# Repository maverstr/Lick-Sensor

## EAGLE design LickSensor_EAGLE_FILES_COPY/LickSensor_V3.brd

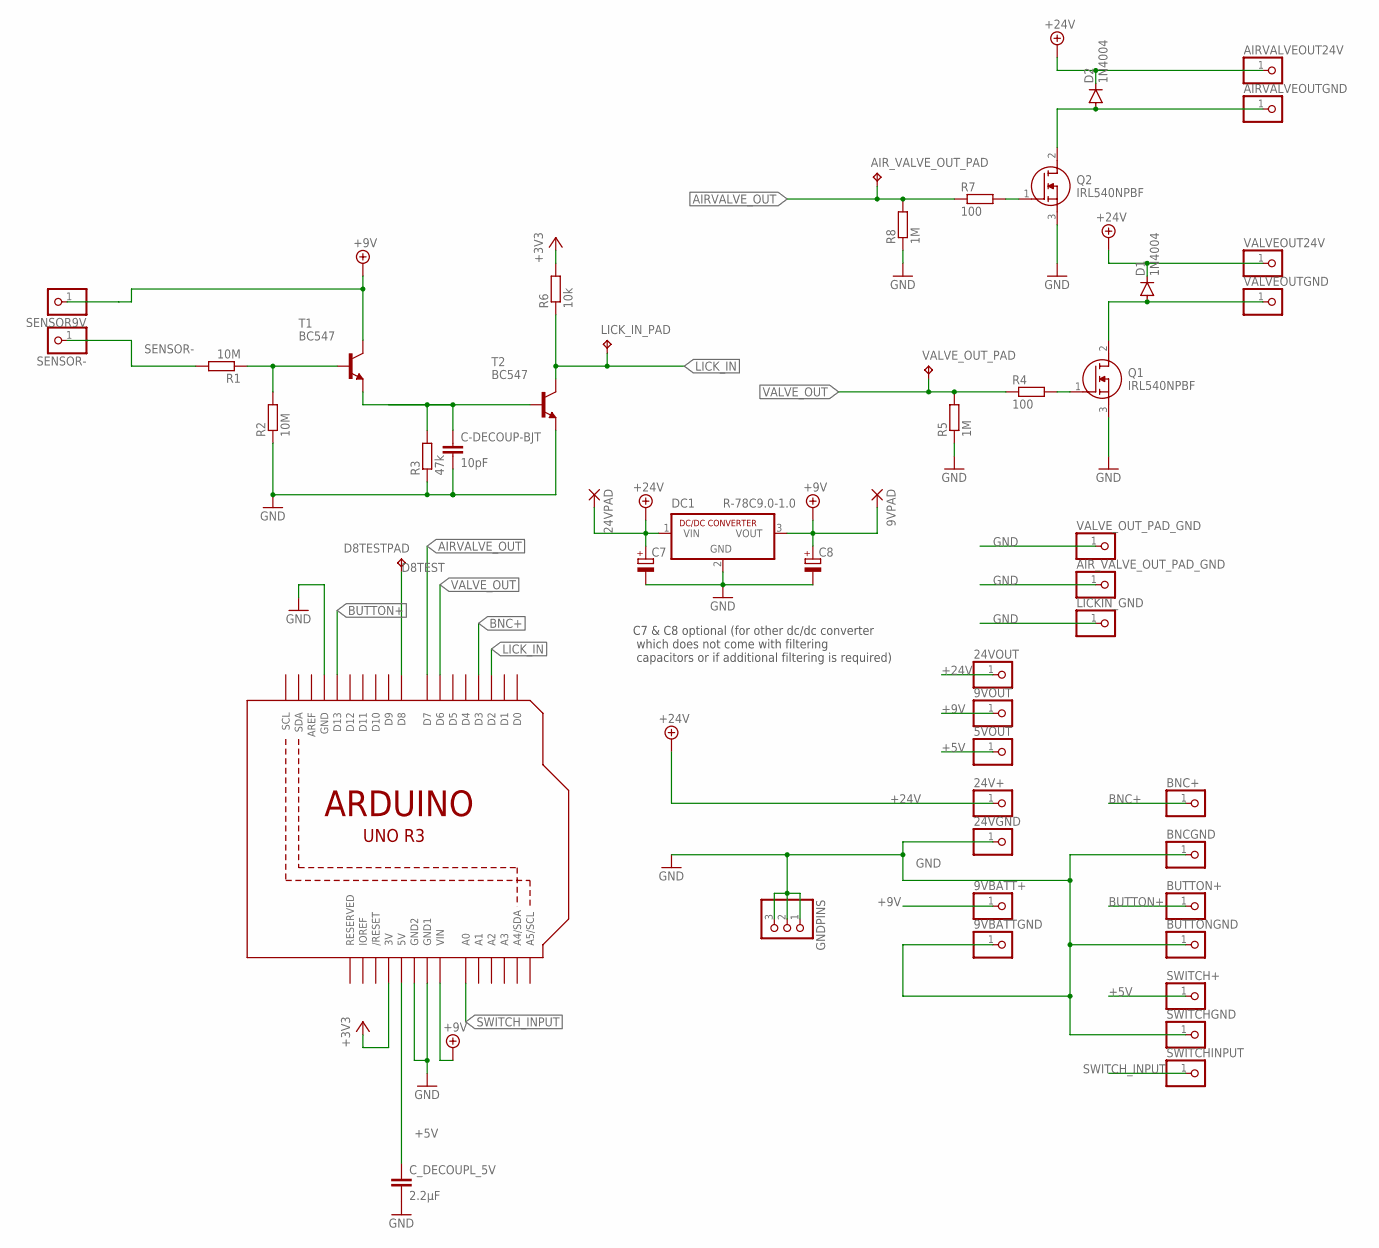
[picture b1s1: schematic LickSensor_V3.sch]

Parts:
5VOUT, 9VBATT+, 9VBATTGND, 9VOUT, 24V+, 24VGND, 24VOUT: PINHD-1X1; 1X01
9VPAD, 24VPAD: 1,6/0,8
AIRVALVEOUT24V: PINHD-1X1; 1X01
AIRVALVEOUTGND: PINHD-1X1; 1X01
AIR_VALVE_OUT_PAD: TPPAD1-13; P1-13
AIR_VALVE_OUT_PAD_GND: PINHD-1X1; 1X01
BNC+: PINHD-1X1; 1X01
BNCGND: PINHD-1X1; 1X01
BUTTON+: PINHD-1X1; 1X01
BUTTONGND: PINHD-1X1; 1X01
C7, C8: CPOL-EUTT2D6; TT2D6
C-DECOUP-BJT: 10pF; C050-030X075
C_DECOUPL_5V: 2.2µF; C050-030X075
D1, D2: 1N4004; DO41-10
D8TESTPAD: TPPAD1-13; P1-13
DC1: R-78C9.0-1.0; SIP3
GNDPINS: PINHD-1X3; 1X03
LICKIN_GND: PINHD-1X1; 1X01
LICK_IN_PAD: TPPAD1-13; P1-13
Q1, Q2: IRL540NPBF; TO254P469X1042X1967-3P
R1, R2: 10M; 0207/7
R3: 47k; 0207/7
R4, R7: 100; 0204/7
R5, R8: 1M; 0204/7
R6: 10k; 0204/7
SENSOR9V: PINHD-1X1; 1X01
SENSOR-: PINHD-1X1; 1X01
SWITCH+: PINHD-1X1; 1X01
SWITCHGND: PINHD-1X1; 1X01
SWITCHINPUT: PINHD-1X1; 1X01
T1, T2: BC547; TO92
U1: ARDUINOR3-DIMENSION; ARDUINOR3
VALVEOUT24V: PINHD-1X1; 1X01
VALVEOUTGND: PINHD-1X1; 1X01
VALVE_OUT_PAD: TPPAD1-13; P1-13
VALVE_OUT_PAD_GND: PINHD-1X1; 1X01

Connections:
+3V3: R6.2, U1.3V
+5V: 5VOUT.1, C_DECOUPL_5V.1, SWITCH+.1, U1.5V
+9V: 9VBATT+.1, 9VOUT.1, 9VPAD.1, C8.+, DC1.3 (VOUT), SENSOR9V.1, T1.3 (C), U1.VIN
+24V: 24V+.1, 24VOUT.1, 24VPAD.1, AIRVALVEOUT24V.1, C7.+, D1.C, D2.C, DC1.1 (VIN), VALVEOUT24V.1
AIRVALVE_OUT: AIR_VALVE_OUT_PAD.TP, R7.1, R8.2, U1.D7
BNC+: BNC+.1, U1.D3
BUTTON+: BUTTON+.1, U1.D13
D8TEST: D8TESTPAD.TP, U1.D8
GND: 9VBATTGND.1, 24VGND.1, AIR_VALVE_OUT_PAD_GND.1, BNCGND.1, BUTTONGND.1, C7.-, C8.-, C-DECOUP-BJT.2, C_DECOUPL_5V.2, DC1.2 (GND), GNDPINS.1, GNDPINS.2, GNDPINS.3, LICKIN_GND.1, Q1.3 (S), Q2.3 (S), R2.1, R3.1, R5.1, R8.1, SWITCHGND.1, T2.1 (E), U1.GND, U1.GND1, U1.GND2, VALVE_OUT_PAD_GND.1
GND1: D1.A, Q1.2 (D), VALVEOUTGND.1
GND2: AIRVALVEOUTGND.1, D2.A, Q2.2 (D)
LICK_IN: LICK_IN_PAD.TP, R6.1, T2.3 (C), U1.D2
unnamed: Q2.1 (G), R7.2
unnamed: Q1.1 (G), R4.2
unnamed: C-DECOUP-BJT.1, R3.2, T1.1 (E), T2.2 (B)
unnamed: R1.1, R2.2, T1.2 (B)
SENSOR-: R1.2, SENSOR-.1
SWITCH_INPUT: SWITCHINPUT.1, U1.A0
VALVE_OUT: R4.1, R5.2, U1.D6, VALVE_OUT_PAD.TP

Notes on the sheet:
C7 & C8 optional (for other dc/dc converter which does not come with filtering capacitors or if additional filtering is required)

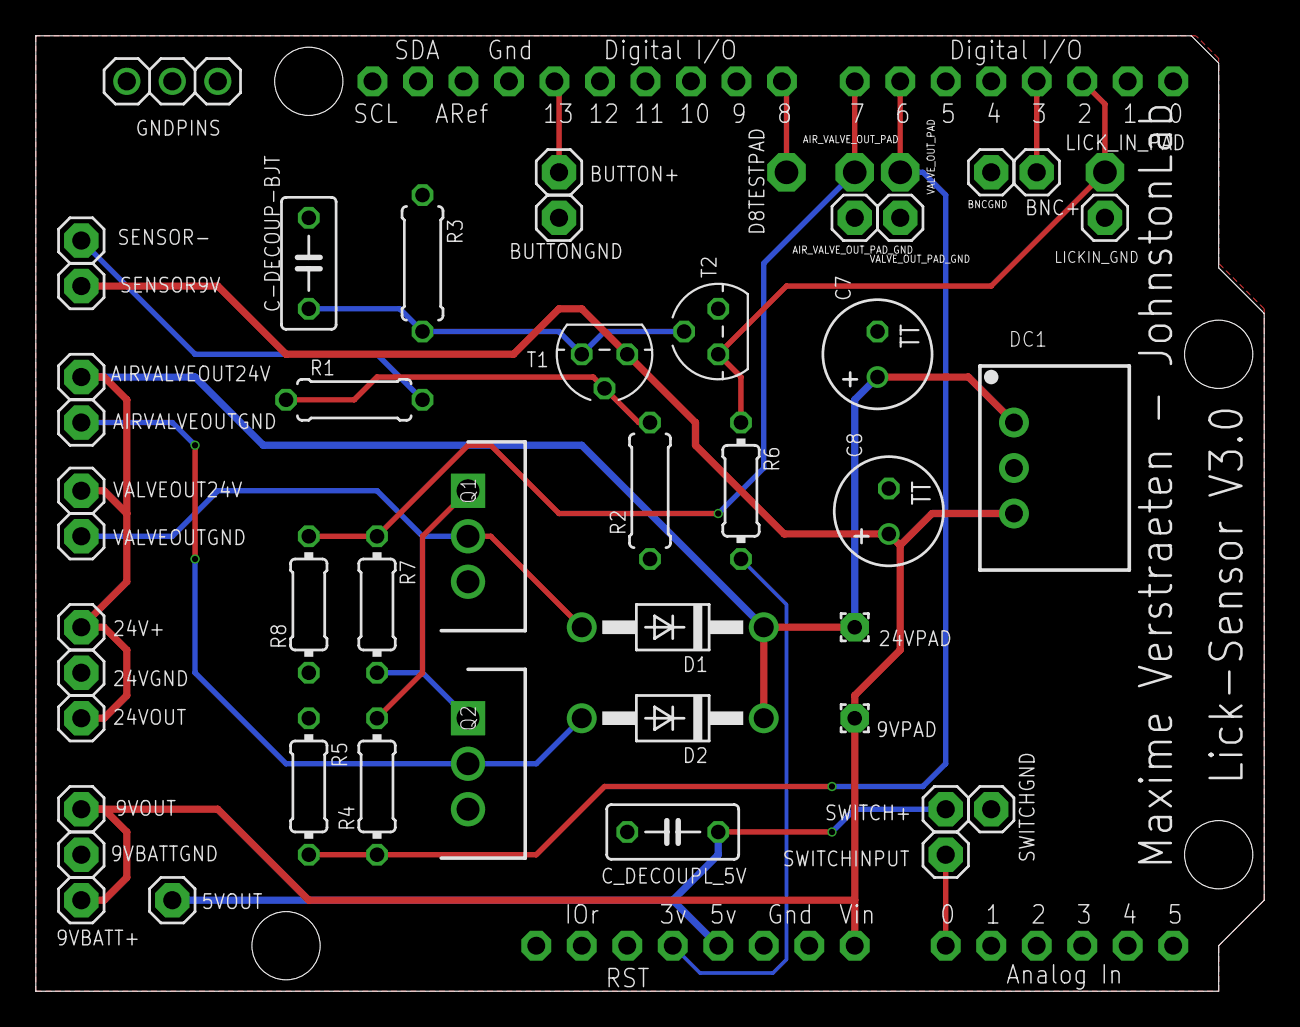
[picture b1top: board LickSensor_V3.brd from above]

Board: 2 copper layers, 68.6 x 53.3 mm, 50 parts (0 on the bottom side), 19 nets.

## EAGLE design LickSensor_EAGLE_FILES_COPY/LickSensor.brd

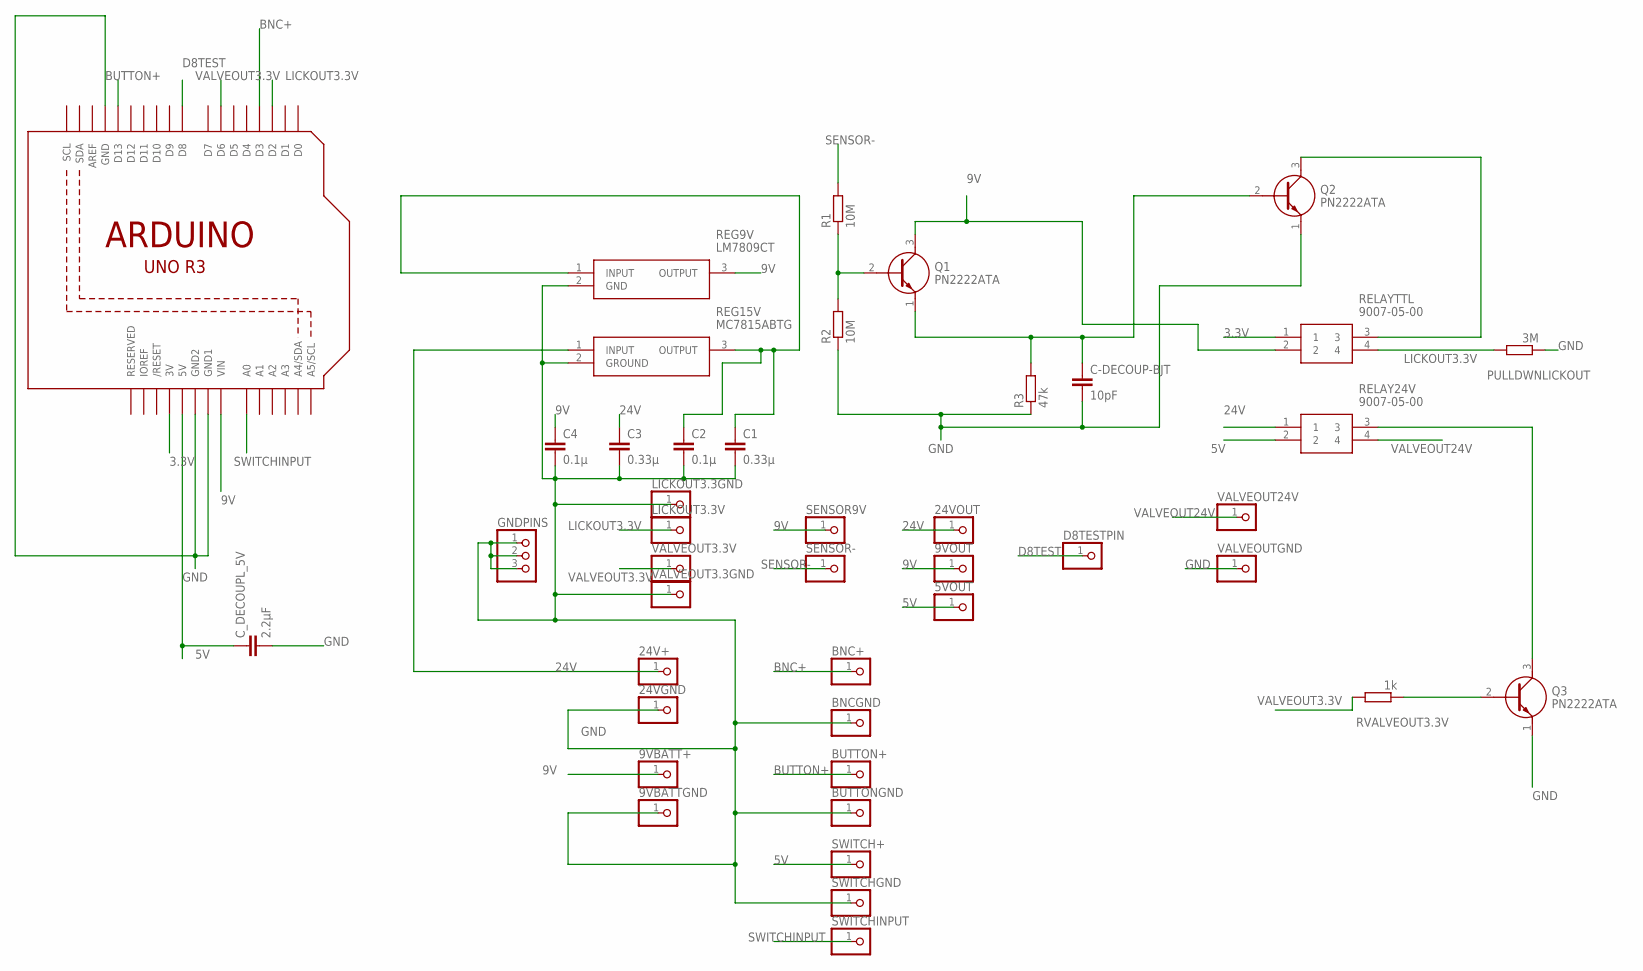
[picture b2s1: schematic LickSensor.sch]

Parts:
5VOUT, 9VBATT+, 9VBATTGND, 9VOUT, 24V+, 24VGND, 24VOUT: PINHD-1X1; 1X01
BNC+: PINHD-1X1; 1X01
BNCGND: PINHD-1X1; 1X01
BUTTON+: PINHD-1X1; 1X01
BUTTONGND: PINHD-1X1; 1X01
C1, C3: 0.33µ; C5B2.5
C2, C4: 0.1µ; C5B2.5
C-DECOUP-BJT: 10pF; C050-030X075
C_DECOUPL_5V: 2.2µF; C050-030X075
D8TESTPIN: PINHD-1X1; 1X01
GNDPINS: PINHD-1X3; 1X03
LICKOUT3.3GND, LICKOUT3.3V: PINHD-1X1; 1X01
PULLDWNLICKOUT: 3M; 0207/10
Q1, Q2, Q3: PN2222ATA; TO-92-3
R1, R2: 10M; 0207/7
R3: 47k; 0207/7
REG9V: LM7809CT; TO254P470X1016X2019-3P
REG15V: MC7815ABTG; TO254P482X997X2018-3P
RELAY24V: 9007-05-00; 9007
RELAYTTL: 9007-05-00; 9007
RVALVEOUT3.3V: 1k; 0207/10
SENSOR9V: PINHD-1X1; 1X01
SENSOR-: PINHD-1X1; 1X01
SWITCH+: PINHD-1X1; 1X01
SWITCHGND: PINHD-1X1; 1X01
SWITCHINPUT: PINHD-1X1; 1X01
U1: ARDUINOR3-DIMENSION; ARDUINOR3
VALVEOUT3.3GND, VALVEOUT3.3V, VALVEOUT24V: PINHD-1X1; 1X01
VALVEOUTGND: PINHD-1X1; 1X01

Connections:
3.3V: RELAYTTL.1, U1.3V
5V: 5VOUT.1, C_DECOUPL_5V.1, RELAY24V.2, SWITCH+.1, U1.5V
9V: 9VBATT+.1, 9VOUT.1, C4.1, Q1.3 (C), REG9V.3 (OUTPUT), RELAYTTL.2, SENSOR9V.1, U1.VIN
24V: 24V+.1, 24VOUT.1, C3.1, REG15V.1 (INPUT), RELAY24V.1
BNC+: BNC+.1, U1.D3
BUTTON+: BUTTON+.1, U1.D13
D8TEST: D8TESTPIN.1, U1.D8
GND: 9VBATTGND.1, 24VGND.1, BNCGND.1, BUTTONGND.1, C1.2, C2.2, C3.2, C4.2, C-DECOUP-BJT.2, C_DECOUPL_5V.2, GNDPINS.1, GNDPINS.2, GNDPINS.3, LICKOUT3.3GND.1, PULLDWNLICKOUT.1, Q2.1 (E), Q3.1 (E), R2.1, R3.1, REG9V.2 (GND), REG15V.2 (GROUND), SWITCHGND.1, U1.GND, U1.GND1, U1.GND2, VALVEOUT3.3GND.1, VALVEOUTGND.1
LICKOUT3.3V: LICKOUT3.3V.1, PULLDWNLICKOUT.2, RELAYTTL.4, U1.D2
unnamed: Q3.2 (B), RVALVEOUT3.3V.1
unnamed: Q3.3 (C), RELAY24V.3
unnamed: C1.1, C2.1, REG9V.1 (INPUT), REG15V.3 (OUTPUT)
unnamed: C-DECOUP-BJT.1, Q1.1 (E), Q2.2 (B), R3.2
unnamed: Q1.2 (B), R1.1, R2.2
unnamed: Q2.3 (C), RELAYTTL.3
SENSOR-: R1.2, SENSOR-.1
SWITCHINPUT: SWITCHINPUT.1, U1.A0
VALVEOUT3.3V: RVALVEOUT3.3V.2, U1.D6, VALVEOUT3.3V.1
VALVEOUT24V: RELAY24V.4, VALVEOUT24V.1

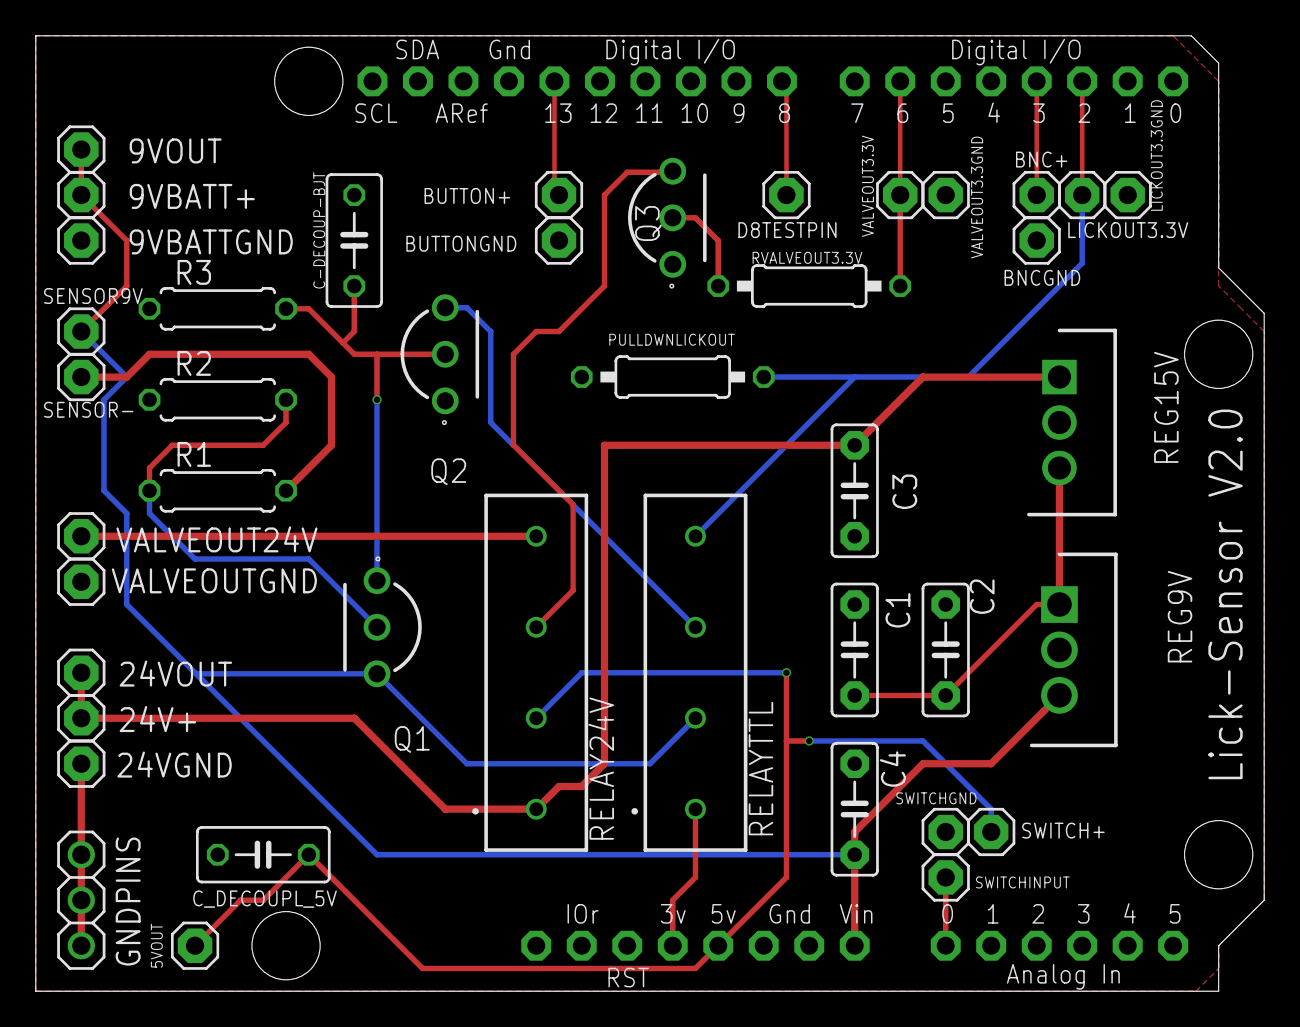
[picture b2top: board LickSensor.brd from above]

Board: 2 copper layers, 68.6 x 53.3 mm, 43 parts (0 on the bottom side), 19 nets.

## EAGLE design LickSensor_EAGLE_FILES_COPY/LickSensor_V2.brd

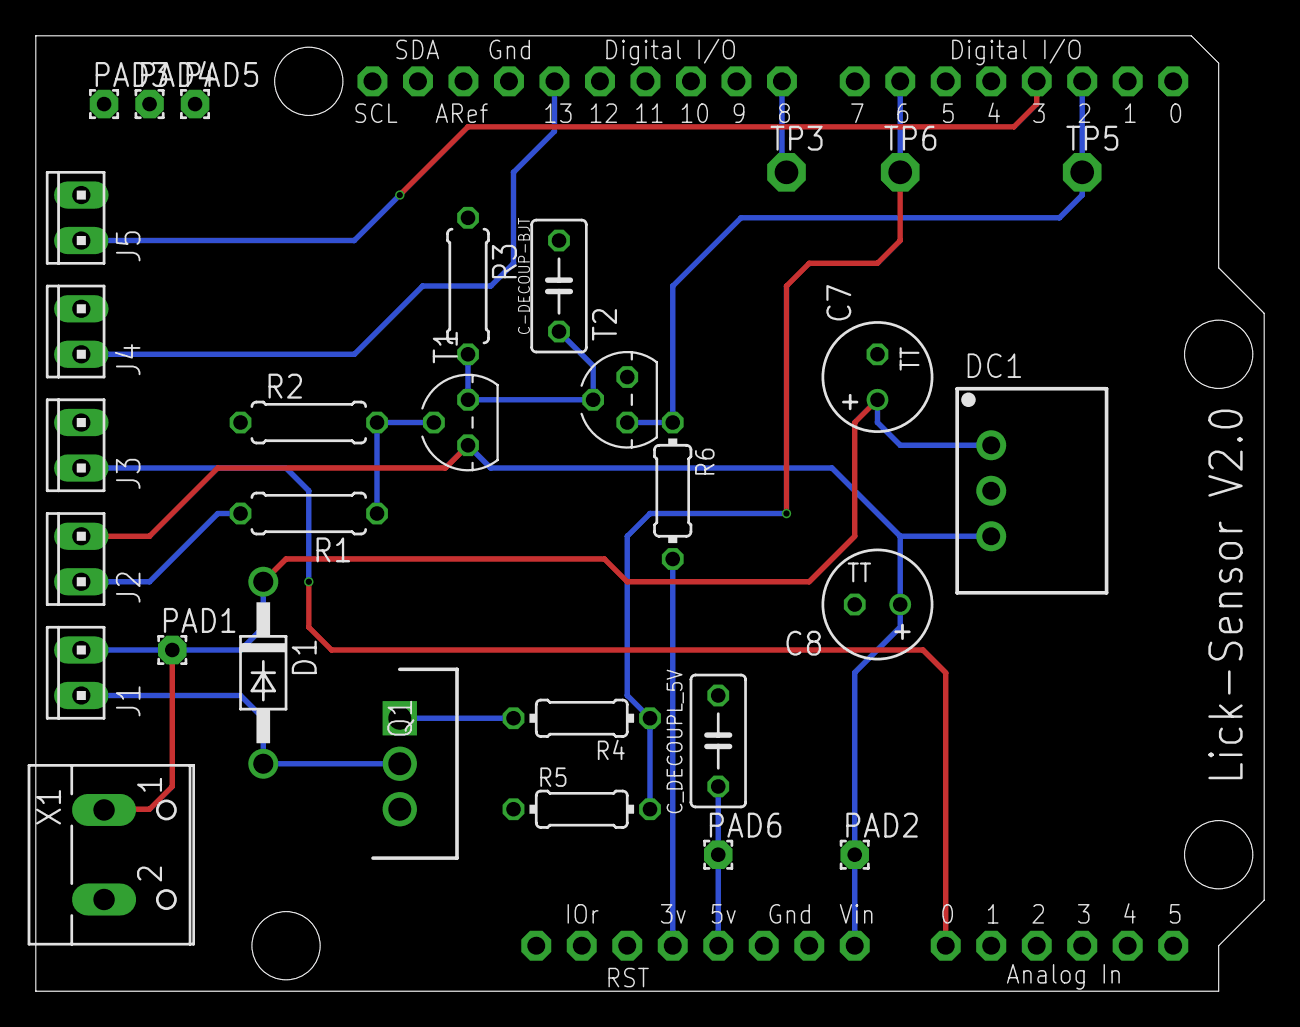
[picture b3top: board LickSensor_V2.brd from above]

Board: 2 copper layers, 68.6 x 53.3 mm, 31 parts (0 on the bottom side), 16 nets.

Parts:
C7, C8: TT2D6
C-DECOUP-BJT: 10pF; C050-030X075
C_DECOUPL_5V: 2.2µF; C050-030X075
D1: 1N4004; DO41-10
DC1: R-78C9.0-1.0; SIP3
J1, J2, J3, J4, J5: 10X02MTA
PAD1, PAD2, PAD3, PAD4, PAD5, PAD6: 1,6/0,8
Q1: IRL540NPBF; TO254P469X1042X1967-3P
R1, R2: 10M; 0207/7
R3: 47k; 0207/7
R4: 100; 0204/7
R5: 1M; 0204/7
R6: 0204/7
T1, T2: BC547; TO92
TP3, TP5, TP6: TPPAD1-13; P1-13
U1: ARDUINOR3-DIMENSION; ARDUINOR3
X1: W237-102

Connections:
5V: C_DECOUPL_5V.1, PAD6.1, U1.5V
+3V3: R6.2, U1.3V
+9V: C8.+, DC1.3, J2.1, PAD2.1, T1.3, U1.VIN
+24V: C7.+, D1.C, DC1.1, J1.1, PAD1.1, X1.1
BNC+: J5.2, U1.D3
BUTTON+: J4.2, U1.D13
D8TEST: TP3.TP, U1.D8
GND: C7.-, C8.-, C-DECOUP-BJT.2, C_DECOUPL_5V.2, DC1.2, J3.1, J4.1, J5.1, PAD3.1, PAD4.1, PAD5.1, Q1.3, R2.1, R3.1, R5.1, T2.1, U1.GND, U1.GND1, U1.GND2, X1.2
LICK_IN: R6.1, T2.3, TP5.TP, U1.D2
unnamed: Q1.1, R4.2
unnamed: D1.A, J1.2, Q1.2
unnamed: C-DECOUP-BJT.1, R3.2, T1.1, T2.2
unnamed: R1.1, R2.2, T1.2
SENSOR-: J2.2, R1.2
SWITCH_INPUT: J3.2, U1.A0
VALVE_OUT: R4.1, R5.2, TP6.TP, U1.D6

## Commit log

2019-08-20 simple lick v1
2019-08-21 added librabry
2019-09-06 release 1.0
2019-09-13 added doc submodule
2019-09-16 added eagle files
2019-09-16 added pdf doc
2019-09-16 added enable interrupt lib
2019-09-18 added auto drain and new workflow
2019-09-23 working proto
2019-09-25 added bill of mat
2019-09-25 updated eagle
2019-09-25 updated eagle files
2019-09-27 updated SW files
2019-10-01 renamed multiple variables + added hardware interface for drain valve
2019-10-01 Added specific debounce delay for toggle switches
2019-10-01 Added init setup for toggle switches
2019-10-03 testing
